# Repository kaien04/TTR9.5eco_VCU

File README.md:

# TTR9.5eco VCU 專案

This is for Taipei Tech Racing TTR9.5eco vehicle VCU project file

## 專案內容
- VCU 相關電路設計圖

## 開發資訊
- 開發者：陳楷恩
- 適用賽事：節能車大賽 / FSAE相關規格參考

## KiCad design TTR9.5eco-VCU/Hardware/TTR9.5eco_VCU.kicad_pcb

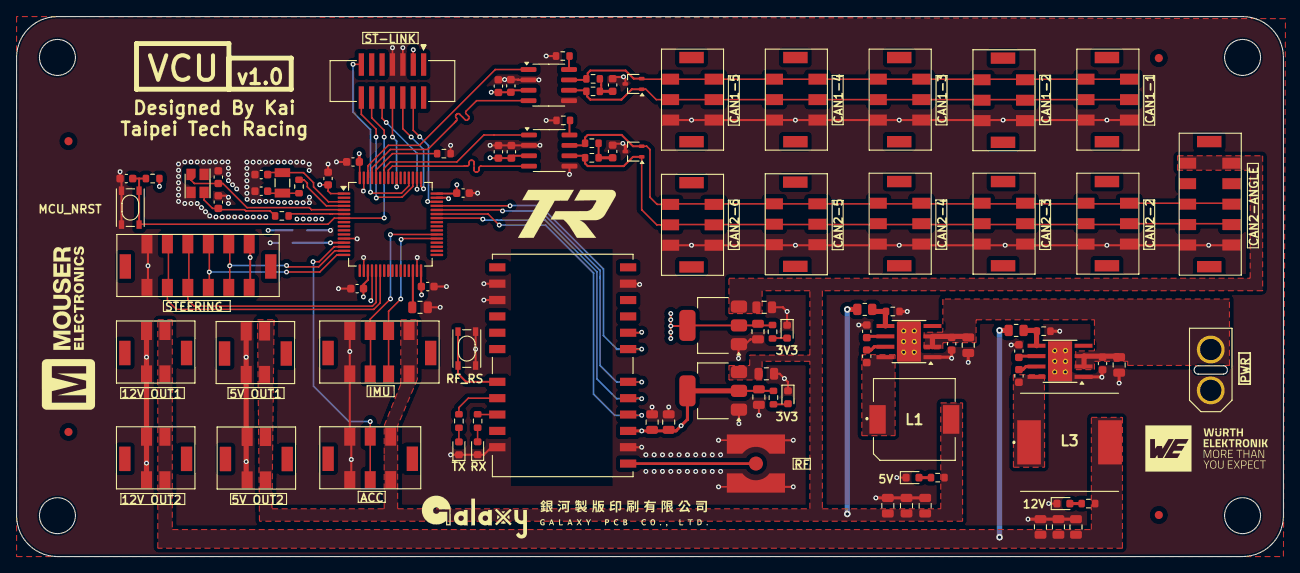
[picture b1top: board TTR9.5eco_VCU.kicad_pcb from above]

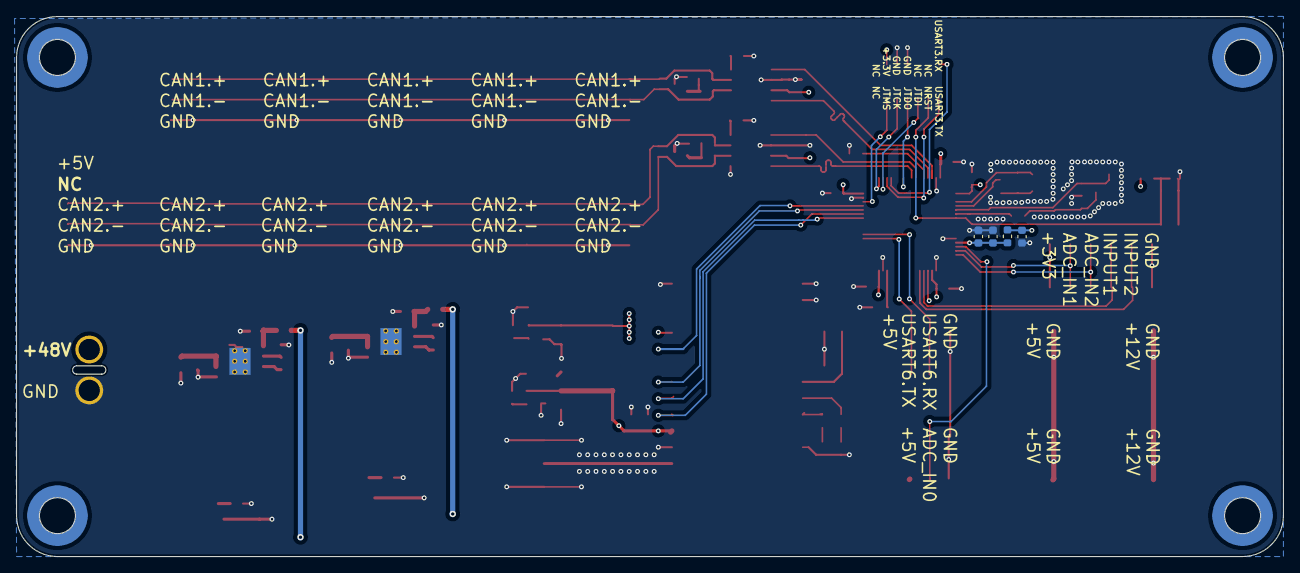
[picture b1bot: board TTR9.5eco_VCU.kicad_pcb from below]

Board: 4 copper layers, 154.9 x 66.0 mm, 112 parts (8 on the bottom side), 64 nets.

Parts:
C1, C31, C41: 4.7μ; C_0805_2012Metric
C2, C3, C4, C5, C6, C7, C10, C12, C16, C20, C25, C42, C43: 0.1μ; C_0603_1608Metric
C8, C9: 4.7μ; C_0603_1608Metric
C11, C13: 4.7n; C_0603_1608Metric
C14, C40: 1μ; C_0805_2012Metric
C17, C22: 2.2μ; C_0805_2012Metric
C18, C23: 220n; C_0603_1608Metric
C19, C24: 1μ; C_0603_1608Metric
C21, C34, C35: 10μ; C_0805_2012Metric
C26, C32, C33: 22μ; C_0805_2012Metric
C27, C28, C29, C30: 14p; C_0603_1608Metric
C112, C113: 47u; C_0805_2012Metric
D1, D2, D3, D6: GLED; LED_0603_1608Metric
D4: RX(RLED); LED_0603_1608Metric
D5: TX(YLED); LED_0603_1608Metric
FID1, FID2, FID3, FID4: Fiducial; Fiducial_1mm_Mask2mm
H1, H2, H3, H4: MountingHole; 786140x0x60
J1, J2: 12V Output; 2159310270
J3: PWR; XT30-F
J4: Steering; 2159310570
J5: VESC1; 2159310370
J6: VESC2; 2159310370
J7: VESC3; 2159310370
J8: VESC4; 2159310370
J9: IMU; 2159310470
J10: CAN1_spare1; 2159310370
J11: CAN2_spare5; 2159310370
J12: CAN2_spare1; 2159310370
J13: CAN2_spare2; 2159310370
J14: CAN2_spare3; 2159310370
J15: CAN2_spare4; 2159310370
J16: RF; 60312102114405
J17, J18: 5V Output; 2159310270
J19: Steering Wheel; 2159310670
J20: ACC; 2159310370
J21: MAIN_DEBUG; 62731420621
L1: 22μ; 7447714220
L2: 1μ; L_0603_1608Metric
L3: 47μ; WE-PD_1260_1245_1280_121054
R1, R2, R8, R12: 10k; R_0603_1608Metric
R3, R11, R13, R14: 59; R_0603_1608Metric
R4, R6: 100k; R_0805_2012Metric
R5: 9.09k; R_0603_1608Metric
R7: 24.9k; R_0603_1608Metric
R9, R10: 0; R_0603_1608Metric
R15: 2k; R_0603_1608Metric
R16: 600; R_0603_1608Metric
R17, R20: 260; R_0603_1608Metric
R18: 287; R_0603_1608Metric
R19: 374; R_0603_1608Metric
SW1, SW5: 434123025826
U1, U2: LMR36510FADDAR; Texas_HTSOP-8-1EP_3.9x4.9mm_P1.27mm_EP2.95x4.9mm_Mask2.4x3.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
U3, U10: LDL1117S33R; SOT-223-3_TabPin2
U4: STM32F446RCTx; LQFP-64_10x10mm_P0.5mm
U5, U7: SN65HVD233-Q1; SOIC-8_3.9x4.9mm_P1.27mm
U6, U8: ESD2CAN24; SOT-323_SC-70
U42: 2607011111000
Y1: 8M; WE-CFPX-180
Y2: 32.768k; WE-CFPX-217

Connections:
+3V3: C2.1, C3.1, C4.1, C5.1, C6.1, C9.1, C10.2, C12.2, C31.1, C42.2, C43.2, J19.1, J21.3, L2.2, R1.2, R17.1, U4.1 (VBAT), U4.19 (VDD), U4.32 (VDD), U4.48 (VDD), U4.64 (VDD), U5.3 (VCC), U7.3 (VCC), U10.2 (Vout)
+3V3A: C41.1, C112.1, C113.1, R20.1, U3.2 (Vout), U42.3 (VCC)
+5V: C14.1, C26.1, C32.1, C33.1, C40.1, J4.5, J9.1, J17.1, J18.1, J20.1, L1.2, R6.1, R16.1, U3.3 (VIN), U10.3 (VIN)
+12V: C21.2, C34.1, C35.1, J1.1, J2.1, L3.2, R4.2, R15.1
+48V: C17.1, C18.2, C22.1, C23.2, J3.1, U1.2 (VIN), U1.3 (EN), U2.2 (VIN), U2.3 (EN)
/CAN Transceiver/CAN1.+: J5.3, J6.3, J7.3, J8.3, J10.3, R3.1, U5.7 (CANH), U6.2
/CAN Transceiver/CAN1.-: J5.2, J6.2, J7.2, J8.2, J10.2, R11.1, U5.6 (CANL), U6.1
/CAN Transceiver/CAN1.RX: U4.61 (PB8), U5.4 (RXD)
/CAN Transceiver/CAN1.TX: U4.62 (PB9), U5.1 (TXD)
/CAN Transceiver/CAN2.+: J4.3, J11.3, J12.3, J13.3, J14.3, J15.3, R13.1, U7.7 (CANH), U8.2
/CAN Transceiver/CAN2.-: J4.2, J11.2, J12.2, J13.2, J14.2, J15.2, R14.1, U7.6 (CANL), U8.1
/CAN Transceiver/CAN2.RX: U4.57 (PB5), U7.4 (RXD)
/CAN Transceiver/CAN2.TX: U4.58 (PB6), U7.1 (TXD)
/Connectors/ACC_SIG: J20.2, U4.14 (PA0)
/Connectors/ROT1_SIG: J19.2, U4.15 (PA1)
/Connectors/ROT2_SIG: J19.3, U4.16 (PA2)
/Connectors/SW1_SIG: J19.4, U4.21 (PA5)
/Connectors/SW2_SIG: J19.5, U4.22 (PA6)
/Connectors/SYS.JTCK: J21.6, U4.49 (PA14)
/Connectors/SYS.JTDI: J21.10, U4.50 (PA15)
/Connectors/SYS.JTDO: J21.8, U4.55 (PB3)
/Connectors/SYS.JTMS: J21.4, U4.46 (PA13)
/Connectors/USART3.RX: J21.13, U4.52 (PC11)
/Connectors/USART3.TX: J21.14, U4.51 (PC10)
/Connectors/USART6.RX: J9.3, U4.38 (PC7)
/Connectors/USART6.TX: J9.2, U4.37 (PC6)
/MCU/NRST: C16.2, J21.12, R1.1, SW1.3, SW1.4, U4.7 (NRST)
/MCU/OSC32_IN: C29.2, U4.3 (PC14), Y2.2
/MCU/OSC32_OUT: R10.2, U4.4 (PC15)
/MCU/OSC_IN: C27.2, U4.5 (PH0), Y1.1
/MCU/OSC_OUT: R9.2, U4.6 (PH1)
/MCU/USART1.CTS: U4.44 (PA11), U42.6 (~RTS)
/MCU/USART1.RTS: U4.45 (PA12), U42.7 (~CTS)
/MCU/USART1.RX: U4.43 (PA10), U42.4 (UTXD)
/MCU/USART1.TX: U4.42 (PA9), U42.5 (URXD)
/MCU/~DATA_IND: U4.20 (PA4), U42.8 (~DATA_IND)
/Radio/RF-50: J16.1 (In), U42.1 (ANT)
GND: C1.2, C2.2, C3.2, C4.2, C5.2, C6.2, C7.2, C8.2, C9.2, C10.1, C11.2, C12.1, C13.2, C14.2, C16.1, C17.2, C18.1, C19.1, C21.1, C22.2, C23.1, C24.1, C26.2, C27.1, C28.1, C29.1, C30.1, C31.2, C32.2, C33.2, C34.2, C35.2, C40.2, C41.2, C42.1, C43.1, C112.2, C113.2, D1.1 (K), D2.1 (K), D3.1 (K), D4.1 (K), D5.1 (K), D6.1 (K), J1.2, J2.2, J3.2, J4.1, J5.1, J6.1, J7.1, J8.1, J9.4, J10.1, J11.1, J12.1, J13.1, J14.1, J15.1, J16.2 (Ext), J17.2, J18.2, J19.6, J20.3, J21.5, J21.7, R2.2, R5.2, R7.2, R8.2, R12.2, SW1.1, SW1.2, SW5.1, SW5.2, U1.1 (PGND), U1.9 (PAD), U2.1 (PGND), U2.9 (PAD), U3.1 (GND), U4.12 (VSSA), U4.18 (VSS), U4.31 (VSS), U4.47 (VSS), U4.63 (VSS), U5.2 (GND), U5.5 (LBK), U6.3, U7.2 (GND), U7.5 (LBK), U8.3, U10.1 (GND), U42.2 (GND), U42.11 (~DATA_REQ), U42.14 (TRX_DISABLE), U42.15 (~CONFIG), U42.23 (GND), Y1.2, Y1.4
unnamed: C11.1, R3.2, R11.2
unnamed: C13.1, R13.2, R14.2
unnamed: C28.2, R9.1, Y1.3
unnamed: C30.2, R10.1, Y2.1
unnamed: D1.2 (A), R16.2
unnamed: D2.2 (A), R15.2
unnamed: D3.2 (A), R17.2
unnamed: D4.2 (A), R18.2
unnamed: D5.2 (A), R19.2
unnamed: D6.2 (A), R20.2
unnamed: C20.1, U1.7 (BOOT)
unnamed: R4.1, R5.1, U1.5 (FB)
unnamed: C20.2, L3.1, U1.8 (SW)
unnamed: C19.2, U1.6 (VCC)
unnamed: C25.1, U2.7 (BOOT)
unnamed: R6.2, R7.1, U2.5 (FB)
unnamed: C25.2, L1.1, U2.8 (SW)
unnamed: C24.2, U2.6 (VCC)
unnamed: R8.1, U4.60 (BOOT0)
unnamed: C1.1, U4.30 (VCAP_1)
unnamed: C7.1, C8.1, L2.1, U4.13 (VDDA)
unnamed: R2.1, U5.8 (RS)
unnamed: R12.1, U7.8 (RS)
unnamed: R18.1, U42.21 (RX_INDICATE)
unnamed: R19.1, U42.20 (TX_INDICATE)
unnamed: SW5.3, SW5.4, U42.19 (~RESET)

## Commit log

2026-05-07 Initial commit: TTR9.5eco 專案初始檔案
2026-05-07 Add README for TTR9.5eco VCU project
2026-05-07 Initial commit: TTR9.5eco_VCU v1
